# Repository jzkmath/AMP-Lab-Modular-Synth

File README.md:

# AMP Lab Modular Synth
This is a fully modular eurorack synthesizer project, where I design all the circuits myself, or do designs based off of existing modules.

All PCBs will be designed in KiCAD so that the entire project can be made open source and used by anyone interested. 

## Important Links:
[AMP Lab Project Page](https://sites.google.com/a/vt.edu/amp_lab/projects/modular-eurorack-synth)

[YuSynth](http://yusynth.net/Modular/modular.html) - Basis for some of the designs

[Moog Werkstatt](https://www.moogmusic.com/products/werkstatt-01) - Basis for some of the designs

## VCO

## VCF

## EG

## VCA

## MIDI Controller

## Power Supply

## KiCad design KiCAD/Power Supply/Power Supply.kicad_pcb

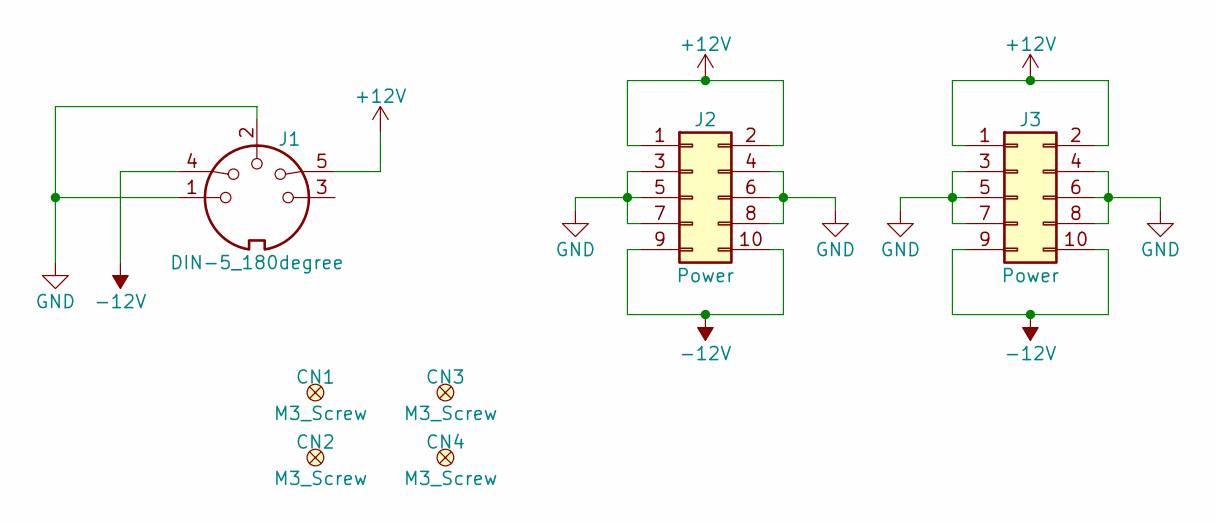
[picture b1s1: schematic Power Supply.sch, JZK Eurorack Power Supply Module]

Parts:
CN1, CN2, CN3, CN4: M3_Screw; M3_Screw_Hole; Digikey PN N/A
J1: DIN-5_180degree; PinHeader_1x05_P2.54mm_Vertical
J2, J3: Power; PinHeader_2x05_P2.54mm_Vertical_Zigzag

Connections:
+12V: J1.5, J2.1, J2.2, J3.1, J3.2
-12V: J1.4, J2.9, J2.10, J3.9, J3.10
GND: J1.1, J1.2, J2.3, J2.4, J2.5, J2.6, J2.7, J2.8, J3.3, J3.4, J3.5, J3.6, J3.7, J3.8

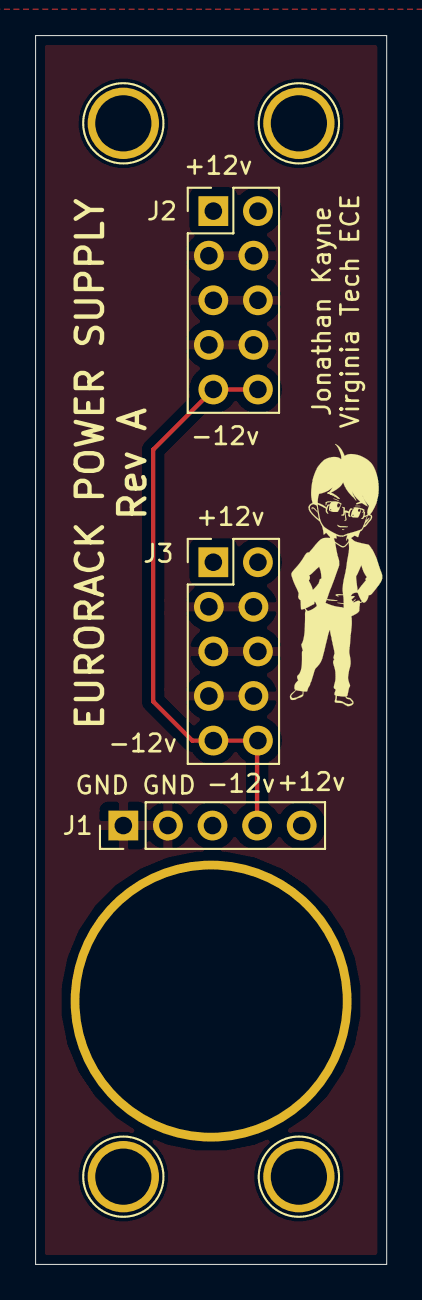
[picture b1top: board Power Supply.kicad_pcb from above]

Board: 2 copper layers, 20.0 x 70.0 mm, 7 parts (0 on the bottom side), 3 nets.

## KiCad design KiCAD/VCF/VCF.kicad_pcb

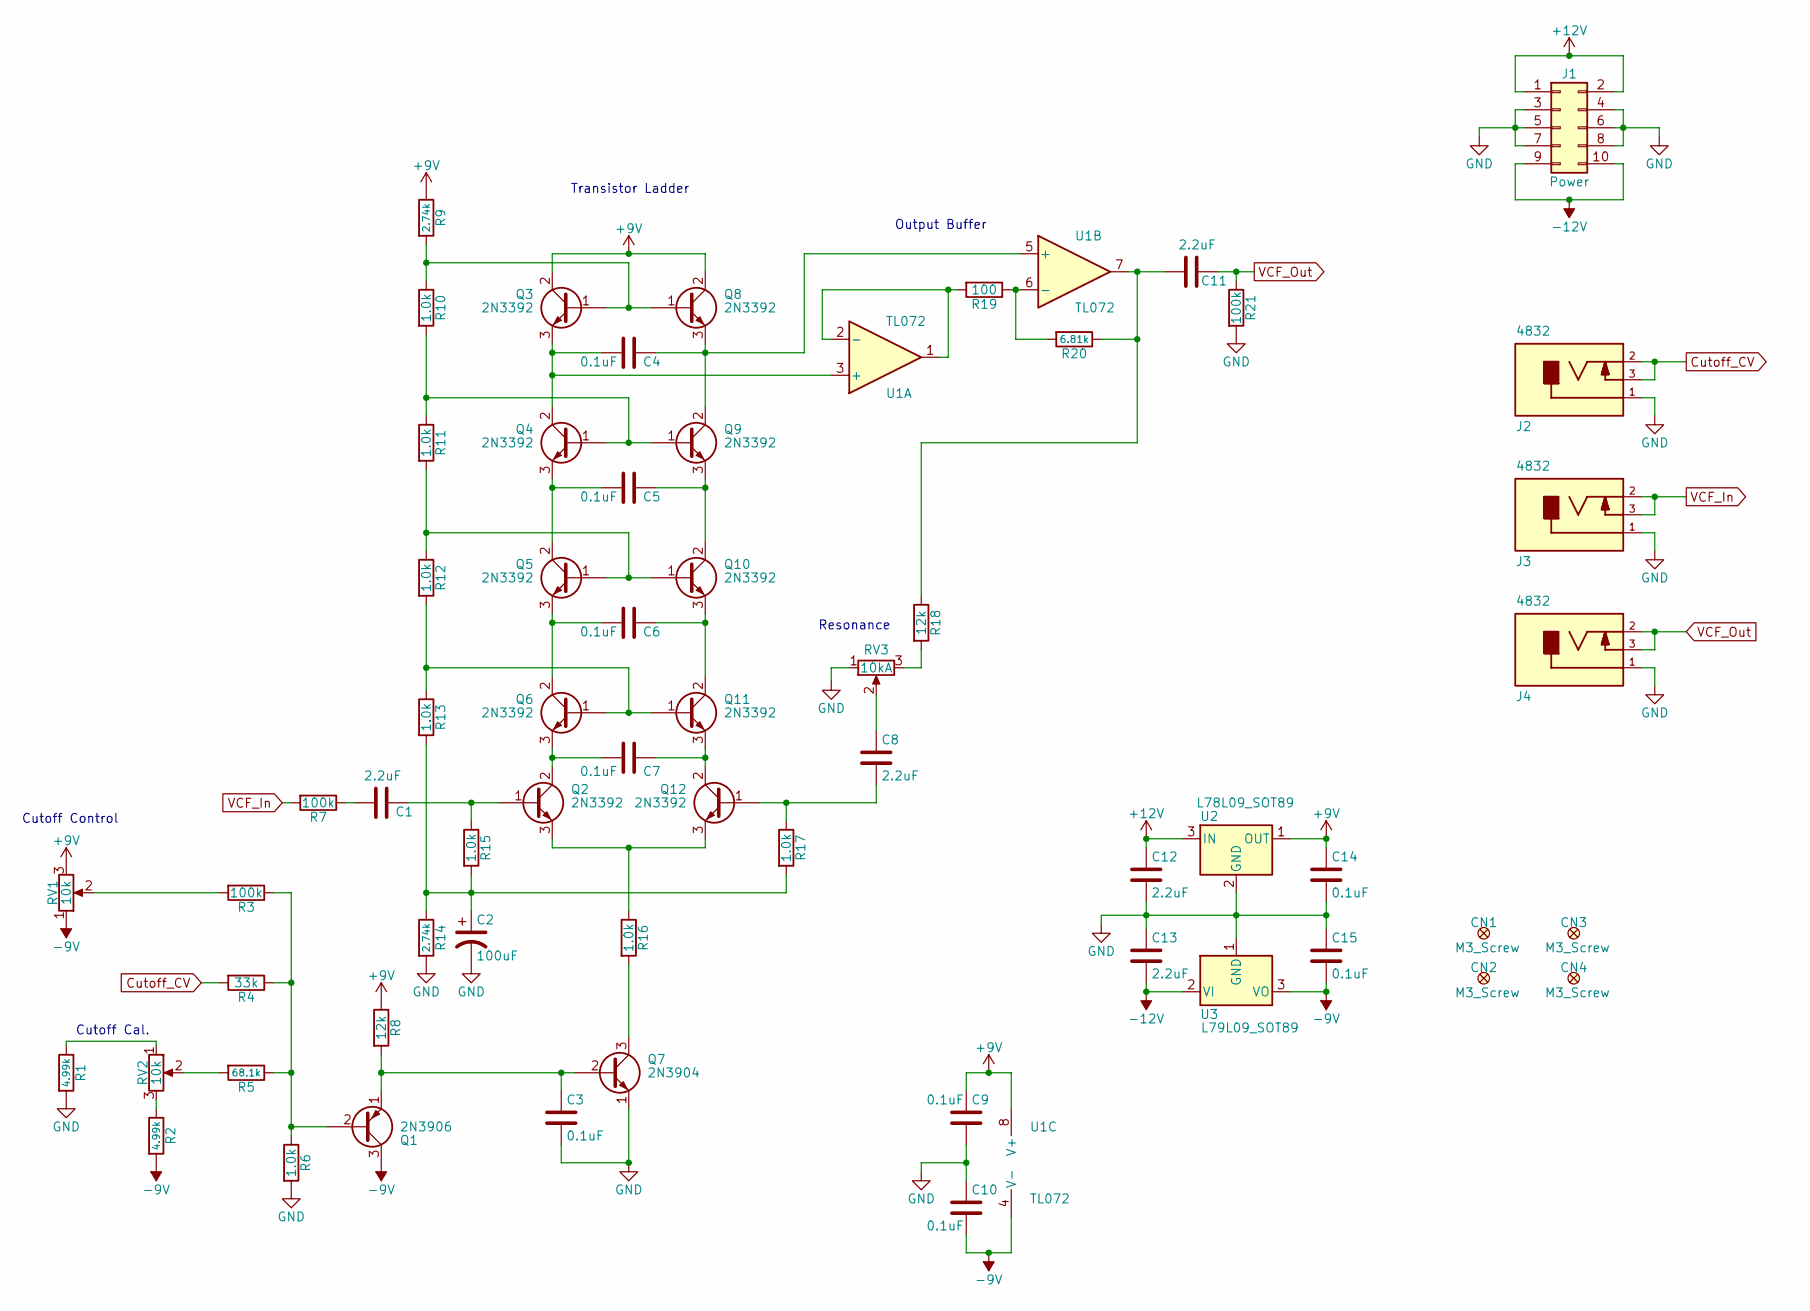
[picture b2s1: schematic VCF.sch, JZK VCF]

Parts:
C1, C8, C11, C12, C13: 2.2uF; C_1206; Digikey PN 1276-1072-1-ND
C2: 100uF; CP_Tantalum_7343; Digikey PN 399-9749-1-ND
C3, C4, C5, C6, C7, C9, C10, C14, C15: 0.1uF; C_1206; Digikey PN 720-1540-1-ND
CN1, CN2, CN3, CN4: M3_Screw; M3_Screw_Hole; Digikey Link N/A
J1: Power; PinHeader_2x05_P2.54mm_Vertical_Zigzag; Digikey PN 609-3243-ND
J2, J3, J4: 4832; Schurter_4832_Jack; Digikey PN 486-3418-ND
Q1: 2N3906; TO-92_HandSolder; Digikey PN 2N3906TARFSCT-ND
Q2, Q3, Q4, Q5, Q6, Q8, Q9, Q10, Q11, Q12: 2N3392; TO-92_HandSolder; Digikey PN 2N3392CS-ND
Q7: 2N3904; TO-92_HandSolder; Digikey PN 2N3904FS-ND
R1, R2: 4.99k; R_1206; Digikey PN RNCP1206FTD4K99CT-ND
R3, R7, R21: 100k; R_1206; Digikey PN A129834CT-ND
R4: 33k; R_1206; Digikey PN RMCF1206JT33K0CT-ND
R5: 68.1k; R_1206; Digikey PN RNCP1206FTD68K1CT-ND
R6, R10, R11, R12, R13, R15, R16, R17: 1.0k; R_1206; Digikey PN 311-1.0KERCT-ND
R8, R18: 12k; R_1206; Digikey PN A129823CT-ND
R9, R14: 2.74k; R_1206; Digikey PN 311-2.74KFRCT-ND
R19: 100; R_1206; Digikey PN RNCP1206FTD100RCT-ND
R20: 6.81k; R_1206; Digikey PN RNCP1206FTD6K81CT-ND
RV1: 10k; Potentiometer_Bourns_PTV09A-1_Single_Vertical; Digikey PN PTV09A-4020F-B103-ND
RV2: 10k; Potentiometer_Piher_PT-10-V10_Vertical; Digikey PN 1993-1104-ND
RV3: 10kA; Potentiometer_Bourns_PTV09A-1_Single_Vertical; Digikey PN PTV09A-4020F-A103-ND
U1: TL072; SOIC-8_3.9x4.9mm_P1.27mm; Digikey PN 296-1282-1-ND
U2: L78L09_SOT89; SOT-89-3; Digikey PN 497-1192-1-ND
U3: L79L09_SOT89; SOT-89-3; Digikey PN NJM79L09UA-TE1CT-ND

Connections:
+9V: C9.1, C14.1, Q3.2 (C), Q8.2 (C), R8.1, R9.1, RV1.3, U1.8 (V+), U2.1 (OUT)
+12V: C12.1, J1.1, J1.2, U2.3 (IN)
-9V: C10.2, C15.2, Q1.3 (C), R2.2, RV1.1, U1.4 (V-), U3.3 (VO)
-12V: C13.2, J1.9, J1.10, U3.2 (VI)
Cutoff_CV: J2.2, J2.3, R4.2
GND: C2.2, C3.2, C9.2, C10.1, C12.2, C13.1, C14.2, C15.1, J1.3, J1.4, J1.5, J1.6, J1.7, J1.8, J2.1, J3.1, J4.1, Q7.1 (E), R1.2, R6.2, R14.2, R21.2, RV3.1, U2.2 (GND), U3.1 (GND)
unnamed: C1.1, Q2.1 (B), R15.1
unnamed: C1.2, R7.1
unnamed: C2.1, R13.2, R14.1, R15.2, R17.2
unnamed: C3.1, Q1.1 (E), Q7.2 (B), R8.2
unnamed: C4.1, Q8.3 (E), Q9.2 (C), U1.5 (+)
unnamed: C4.2, Q3.3 (E), Q4.2 (C), U1.3 (+)
unnamed: C5.1, Q9.3 (E), Q10.2 (C)
unnamed: C5.2, Q4.3 (E), Q5.2 (C)
unnamed: C6.1, Q10.3 (E), Q11.2 (C)
unnamed: C6.2, Q5.3 (E), Q6.2 (C)
unnamed: C7.1, Q11.3 (E), Q12.2 (C)
unnamed: C7.2, Q2.2 (C), Q6.3 (E)
unnamed: C8.1, RV3.2
unnamed: C8.2, Q12.1 (B), R17.1
unnamed: C11.2, R18.1, R20.1, U1.7
unnamed: Q1.2 (B), R3.1, R4.1, R5.1, R6.1
unnamed: Q3.1 (B), Q8.1 (B), R9.2, R10.1
unnamed: Q4.1 (B), Q9.1 (B), R10.2, R11.1
unnamed: Q7.3 (C), R16.2
unnamed: Q5.1 (B), Q10.1 (B), R11.2, R12.1
unnamed: Q6.1 (B), Q11.1 (B), R12.2, R13.1
unnamed: Q2.3 (E), Q12.3 (E), R16.1
unnamed: R1.1, RV2.1
unnamed: R2.1, RV2.3
unnamed: R3.2, RV1.2
unnamed: R5.2, RV2.2
unnamed: R18.2, RV3.3
unnamed: R19.1, R20.2, U1.6 (-)
unnamed: R19.2, U1.1, U1.2 (-)
VCF_In: J3.2, J3.3, R7.2
VCF_Out: C11.1, J4.2, J4.3, R21.1

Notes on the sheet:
Cutoff Control
Cutoff Cal.
Transistor Ladder
Output Buffer
Resonance

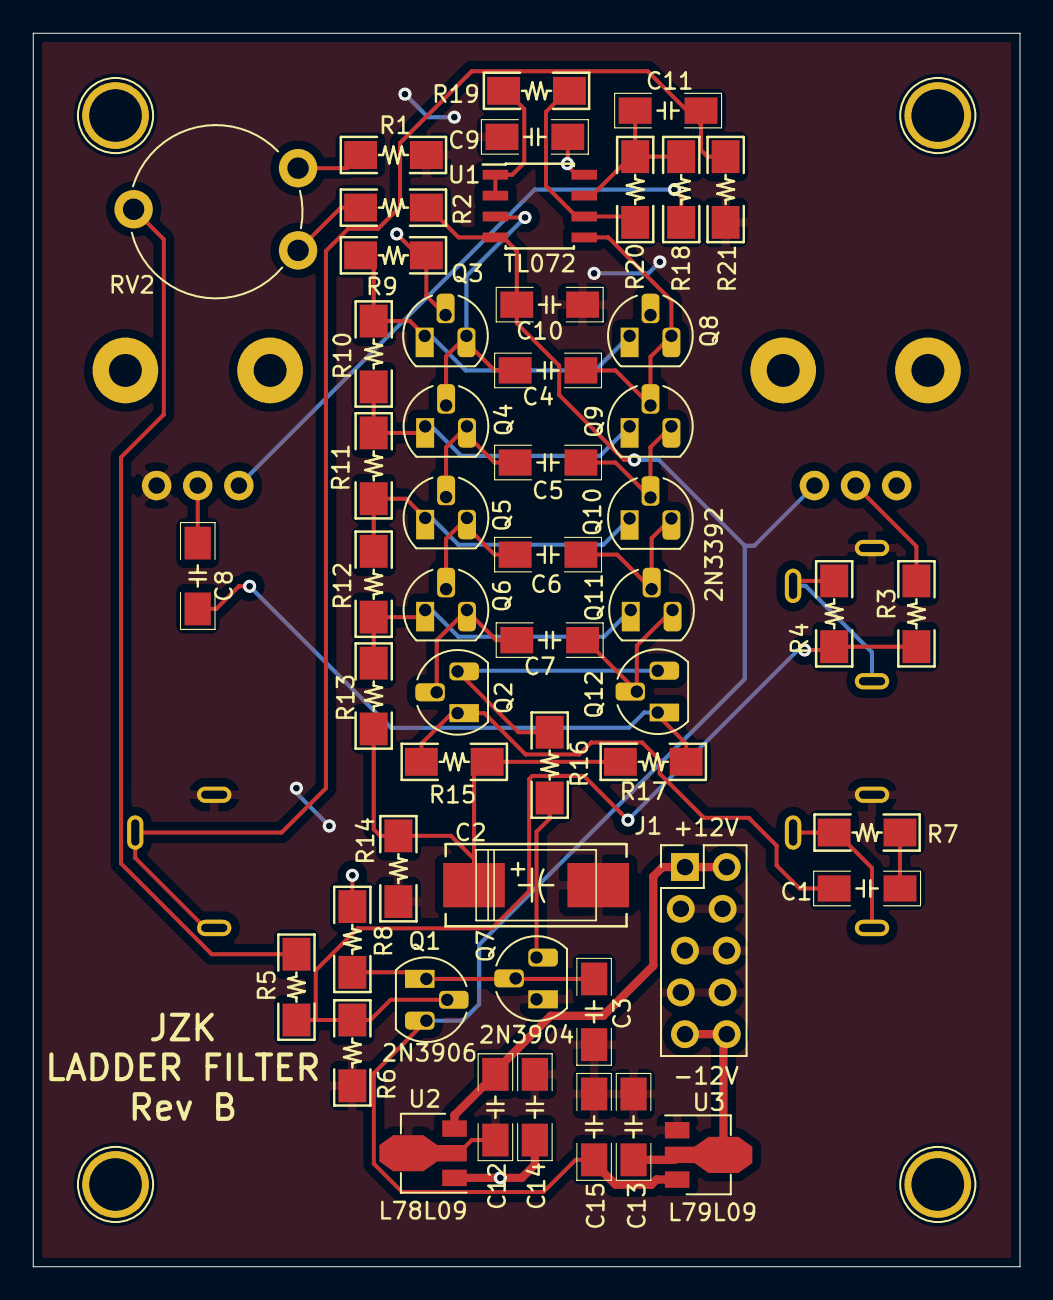
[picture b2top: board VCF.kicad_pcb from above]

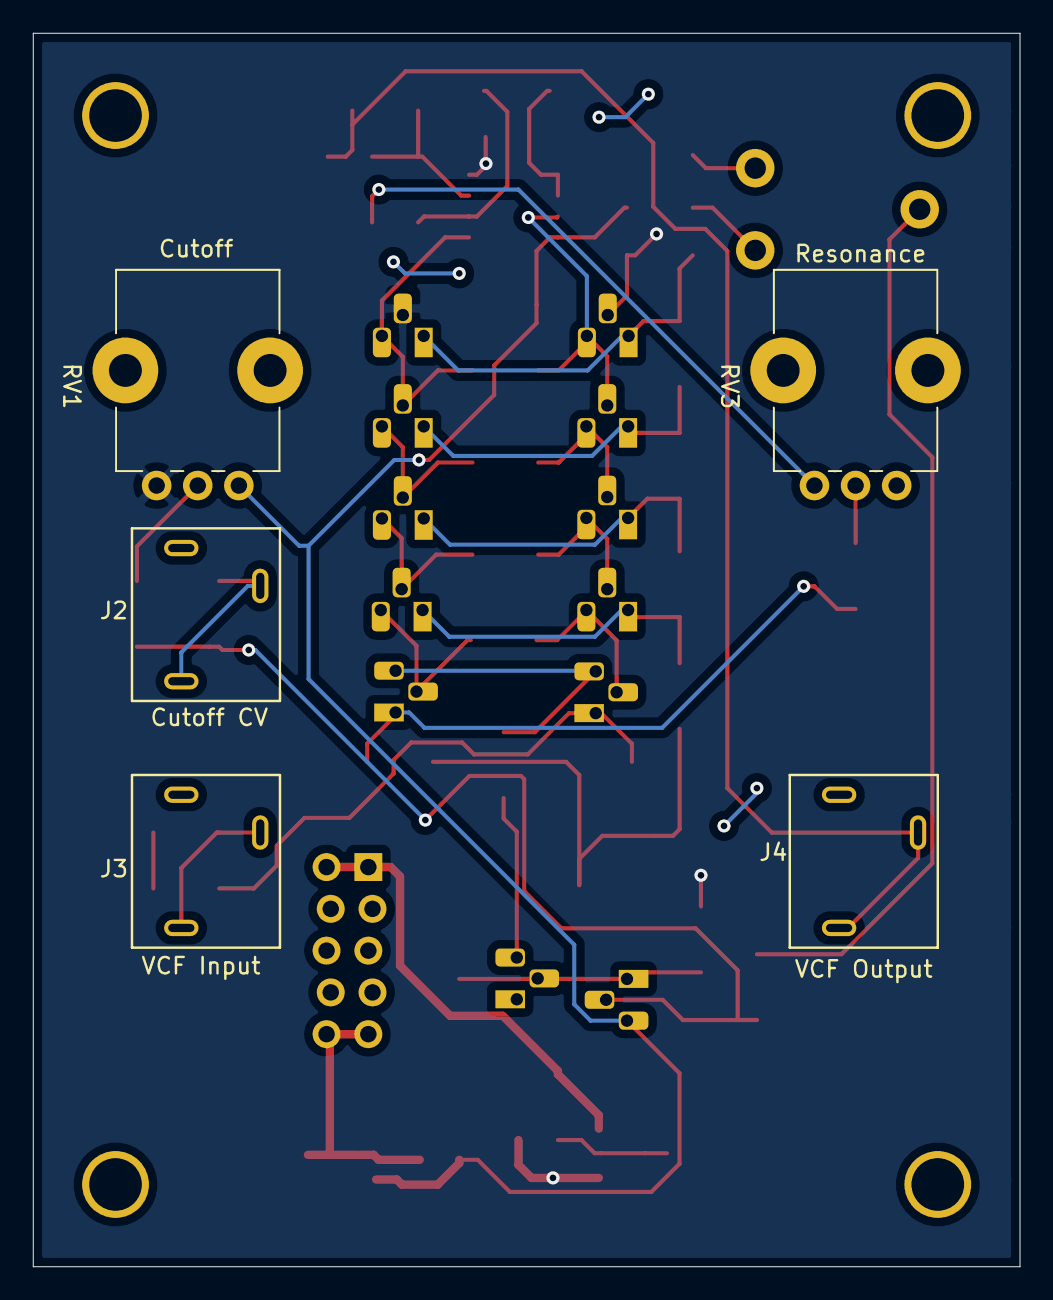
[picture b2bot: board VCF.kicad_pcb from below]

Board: 2 copper layers, 60.0 x 75.0 mm, 62 parts (5 on the bottom side), 37 nets.

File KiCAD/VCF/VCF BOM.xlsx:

Item | Qty | Reference(s) | Value | Footprint | Cost ea | Total Cost | Digikey PN | Link | Total: | 22.346000000000011
1 | 5 | C1, C8, C11-C13 | 2.2uF | SMD 1206 | 0.22 | 1.1000000000000001 | 1276-1072-1-ND | https://www.digikey.com/short/pzvv0r
2 | 1 | C2 | 100uF | SMD 7343 | 2.71 | 2.71 | 399-9749-1-ND | https://www.digikey.com/short/pzvvbz
3 | 9 | C3-C7, C9, C10, C14, C15 | 0.1uF | SMD 1206 | 8.7999999999999995E-2 | 0.79199999999999993 | 1276-1017-1-ND | https://www.digikey.com/short/pzb5jq
4 | 1 | J1 | Power | 2x5 Header | 0.28000000000000003 | 0.28000000000000003 | 609-3243-ND | https://www.digikey.com/short/pzbbv4
5 | 3 | J2-J4 | MJ-3502 | HP Jack | 1.5 | 4.5 | 486-3418-ND | https://www.digikey.com/short/pzbbdf
6 | 1 | Q1 | 2N3906 | TO-92 | 0.24 | 0.24 | 2N3906TARFSCT-ND | https://www.digikey.com/short/pzvv5n
7 | 10 | Q2-Q6, Q8-Q12 | 2N3392 | TO-92 | 0.66800000000000004 | 6.6800000000000006 | 2N3392CS-ND | https://www.digikey.com/short/pzvv5p
8 | 1 | Q7 | 2N3904 | TO-92 | 0.21 | 0.21 | 2N3904FS-ND | https://www.digikey.com/short/pzvv5m
9 | 2 | R1, R2 | 4.99k | SMD 1206 | 0.1 | 0.2 | RNCP1206FTD4K99CT-ND | https://www.digikey.com/short/pzvvn3
10 | 3 | R3, R7, R21 | 100k | SMD 1206 | 7.0000000000000007E-2 | 0.21000000000000002 | A129834CT-ND | https://www.digikey.com/short/pzb5r0
11 | 1 | R4 | 33k | SMD 1206 | 0.1 | 0.1 | RMCF1206JT33K0CT-ND | https://www.digikey.com/short/pzbr3z
12 | 1 | R5 | 68.1k | SMD 1206 | 0.1 | 0.1 | RNCP1206FTD68K1CT-ND | https://www.digikey.com/short/pzvvnh
13 | 8 | R6, R10-R13, R15-R17 | 1.0k | SMD 1206 | 9.2999999999999999E-2 | 0.74399999999999999 | RNCP1206FTD1K00CT-ND | https://www.digikey.com/short/pzvvnv
14 | 2 | R8, R18 | 12k | SMD 1206 | 0.1 | 0.2 | A129823CT-ND | https://www.digikey.com/short/pzvvdq
15 | 2 | R9, R14 | 2.74k | SMD 1206 | 0.1 | 0.2 | 311-2.74KFRCT-ND | https://www.digikey.com/short/pzvvd5
16 | 1 | R19 | 100 ohm | SMD 1206 | 0.1 | 0.1 | RNCP1206FTD100RCT-ND | https://www.digikey.com/short/pzvvdd
17 | 1 | R20 | 6.81k | SMD 1206 | 0.1 | 0.1 | RNCP1206FTD6K81CT-ND | https://www.digikey.com/short/pzvv07
18 | 2 | RV1, RV3 | 25k | THT Pot | 0.79 | 1.58 | 987-1726-ND | https://www.digikey.com/short/pzb2f3
19 | 1 | RV2 | 10k | Trimpot | 0.46 | 0.46 | 1993-1104-ND | https://www.digikey.com/short/pzzwhq
20 | 1 | U1 | TL072 | SOIC8 | 0.62 | 0.62 | 296-1282-1-ND | https://www.digikey.com/short/pzvvrz
21 | 1 | U2 | L78L09 | SOT-89 | 0.42 | 0.42 | 497-1192-1-ND | https://www.digikey.com/short/pz1hnp
22 | 1 | U3 | L79L09 | SOT-89 | 0.8 | 0.8 | NJM79L09UA-TE1CT-ND | https://www.digikey.com/short/pz1hn5
 |  |  |  |  |  | 0
 |  |  |  |  |  | 0

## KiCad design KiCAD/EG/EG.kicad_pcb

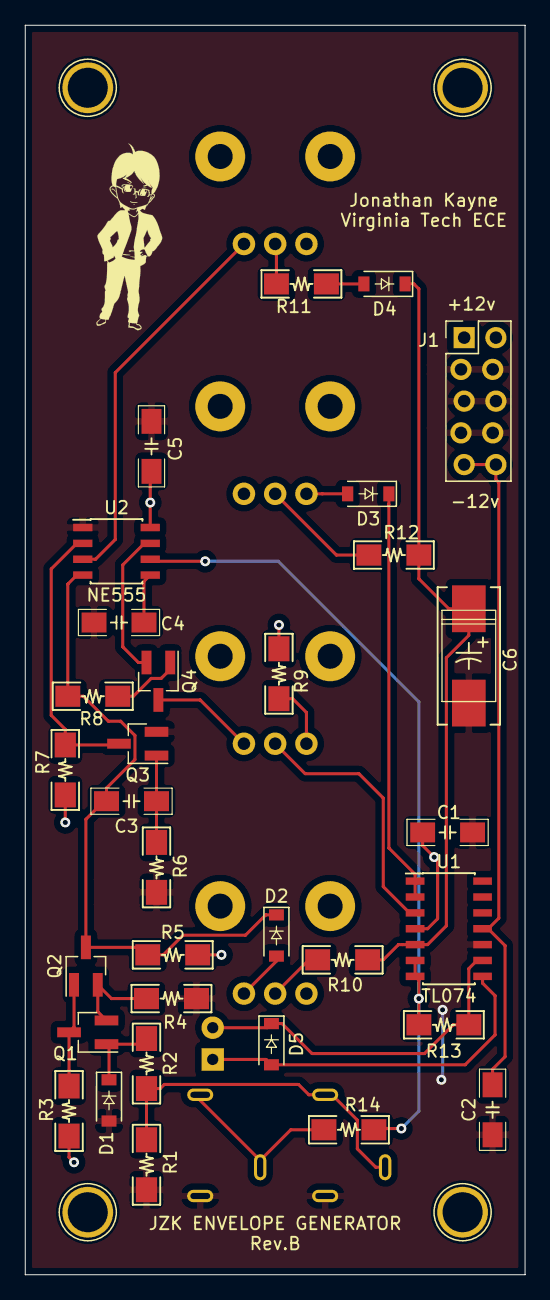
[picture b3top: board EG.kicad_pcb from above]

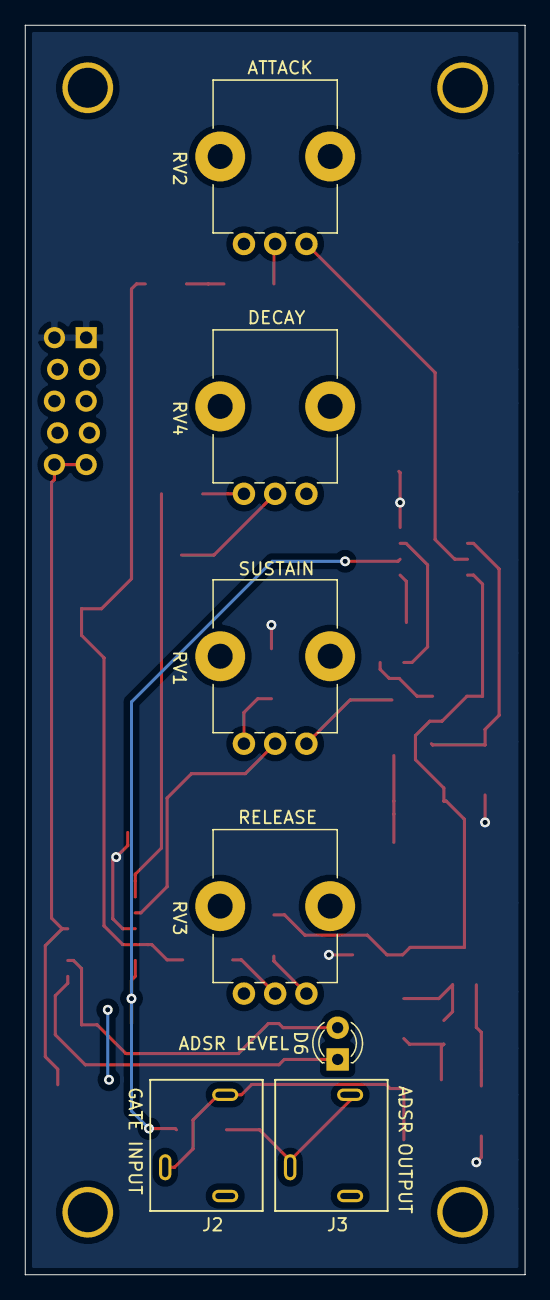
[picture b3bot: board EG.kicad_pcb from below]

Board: 2 copper layers, 40.0 x 100.0 mm, 43 parts (7 on the bottom side), 29 nets.

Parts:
C1, C2, C5: 0.1uF; C_1206
C3, C4: 10nF; C_1206
C6: 10uF; CP_Tantalum_7343
CN1, CN2, CN3, CN4: M3_Screw; M3_Screw_Hole
D1, D2, D3, D4, D5: 1N4148W; D_SOD-123
D6: LED; LED_D3.0mm_Clear
J1: Power; PinHeader_2x05_P2.54mm_Vertical_Zigzag
J2, J3: 4832; Schurter_4832_Jack
Q1, Q2, Q3: BC847; SOT-23_Handsoldering
Q4: 2N7002; SOT-23_Handsoldering
R1: 1.2M; R_1206
R2, R8: 1M; R_1206
R3, R5, R6, R7: 22k; R_1206
R4: 10; R_1206
R9: 4.7k; R_1206
R10, R11, R12: 100; R_1206
R13, R14: 1k; R_1206
RV1: 25k; Potentiometer_Bourns_PTV09A-1_Single_Vertical
RV2, RV3, RV4: 1M Log; Potentiometer_Bourns_PTV09A-1_Single_Vertical
U1: TL074; SOIC-14_3.9x8.7mm_P1.27mm
U2: NE555; SOIC-8_3.9x4.9mm_P1.27mm

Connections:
+12V: C1.1, C5.2, J1.1, J1.2, R3.1, R5.1, R7.1, R9.1, U1.4, U2.8
-12V: C2.2, J1.9, J1.10, U1.11
/Attack: R11.2, RV2.2
/Decay: R12.1, RV4.2
/Release: R10.2, RV3.2
/Sustain: RV1.2, U1.3
ADSR_Out: J3.2, J3.3, R14.1
EG_Out: R13.2, R14.2, U1.6, U1.7, U2.6
GND: C1.2, C2.1, C4.2, C5.1, C6.2, D1.2, J1.3, J1.4, J1.5, J1.6, J1.7, J1.8, J2.1, J3.1, Q3.2, R1.2, R4.2, R6.2, U1.10, U2.1
Gate_In: J2.2, J2.3, R1.1, R2.2
unnamed: C3.1, Q3.1, R6.1
unnamed: C3.2, D2.1, Q2.3, R5.2, R8.2, U2.4
unnamed: C4.1, U2.5
unnamed: C6.1, D4.1, R10.1, R12.2, U1.5
unnamed: D1.1, Q1.1, R2.1
unnamed: D2.2, RV3.1
unnamed: D3.1, U1.1, U1.2
unnamed: D3.2, RV4.3
unnamed: D4.2, R11.1
unnamed: D5.1, D6.2, R13.1, U1.9
unnamed: D5.2, D6.1, U1.8
unnamed: Q1.2, Q2.2, R4.1
unnamed: Q1.3, Q2.1, R3.2
unnamed: Q3.3, R7.2, U2.2
unnamed: Q4.1, R8.1
unnamed: Q4.2, U2.7
unnamed: Q4.3, RV1.1
unnamed: R9.2, RV1.3
unnamed: RV2.1, U2.3

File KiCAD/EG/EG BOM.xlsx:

Item | Qty | Reference(s) | Value | Footprint | Cost ea | Total Cost | Digikey | Link | Final Cost: | 12.316999999999998
1 | 3 | C1, C2, C5 | 0.1uF | SMD 1206 | 8.7999999999999995E-2 | 0.26400000000000001 | 1276-1017-1-ND | https://www.digikey.com/short/pzb5jq |  |  |  | p
2 | 2 | C3, C4 | 10nF | SMD 1206 | 0.27 | 0.54 | 311-1174-1-ND | https://www.digikey.com/short/p47c0p |  |  |  | p
3 | 1 | C6 | 10uF | SMD 7343 | 0.73 | 0.73 | 718-1046-1-ND | https://www.digikey.com/short/p47cw2 |  |  |  | p
4 | 5 | D1-D5 | 1N4148W | SOD-123 | 0.125 | 0.625 | 1N4148WTPMSCT-ND | https://www.digikey.com/short/pzz2zr |  |  |  | p
5 | 1 | D6 | LED | LED | 0 | 0 | Already Have
6 | 1 | J1 | Power | 2x5 Header | 0.28000000000000003 | 0.28000000000000003 | 609-3243-ND | https://www.digikey.com/short/pzbbv4 |  |  |  | p
7 | 2 | J2, J3 | MJ-3502 | HP Jack | 1.5 | 3 | 486-3418-ND | https://www.digikey.com/short/pzbbdf |  |  |  | p
8 | 3 | Q1, Q2, Q3 | BC847 | SOT-23 | 0.129 | 0.38700000000000001 | BC847CLT1GOSCT-ND | https://www.digikey.com/short/p47c90 |  |  |  | p
9 | 1 | Q4 | 2N7002 | SOT-23 | 0.39 | 0.39 | 2N7002NCT-ND | https://www.digikey.com/short/p47cfq |  |  |  | p
10 | 1 | R1 | 1.2M | SMD 1206 | 0.1 | 0.1 | 311-1.20MFRCT-ND | https://www.digikey.com/short/p477qb |  |  |  | p
11 | 2 | R2, R8 | 1M | SMD 1206 | 0.1 | 0.2 | RMCF1206JT1M00CT-ND | https://www.digikey.com/short/pzbrq5 |  |  |  | p
12 | 4 | R3, R5-R7 | 22k | SMD 1206 | 0.27800000000000002 | 1.1120000000000001 | A130554CT-ND | https://www.digikey.com/short/p477jj |  |  |  | p
13 | 1 | R4 | 10 ohm | SMD 1206 | 0.17 | 0.17 | P10ALCT-ND | https://www.digikey.com/short/pzbrph |  |  |  | p
14 | 1 | R9 | 4.7k | SMD 1206 | 0.1 | 0.1 | A130181CT-ND | https://www.digikey.com/short/pzbrh2 |  |  |  | p
15 | 3 | R10-R12 | 100 ohm | SMD 1206 | 0.1 | 0.30000000000000004 | RNCP1206FTD100RCT-ND | https://www.digikey.com/short/pzvvdd |  |  |  | p
16 | 2 | R13, R14 | 1k | SMD 1206 | 0.1 | 0.2 | 311-1.0KERCT-ND | https://www.digikey.com/short/pzbr9h |  |  |  | p
17 | 1 | RV1 | 25k | Pot | 0.79 | 0.79 | 987-1726-ND | https://www.digikey.com/short/pzb2f3 |  |  |  | p
18 | 3 | RV2-RV4 | 1M Log | Pot | 0.71299999999999997 | 2.1389999999999998 | 987-1719-ND | https://www.digikey.com/short/p477bw |  |  |  | p
19 | 1 | U1 | TL074 | SOIC-14 | 0.51 | 0.51 | 296-1283-1-ND | https://www.digikey.com/short/pzz2fn |  |  |  | p
20 | 1 | U2 | NE555 | SOIC-8 | 0.48 | 0.48 | 296-6501-1-ND | https://www.digikey.com/short/p47c41 |  |  |  | p
 |  |  |  |  |  | 0
 |  |  |  |  |  | 0
 |  |  |  |  |  | 0
 |  |  |  |  |  | 0

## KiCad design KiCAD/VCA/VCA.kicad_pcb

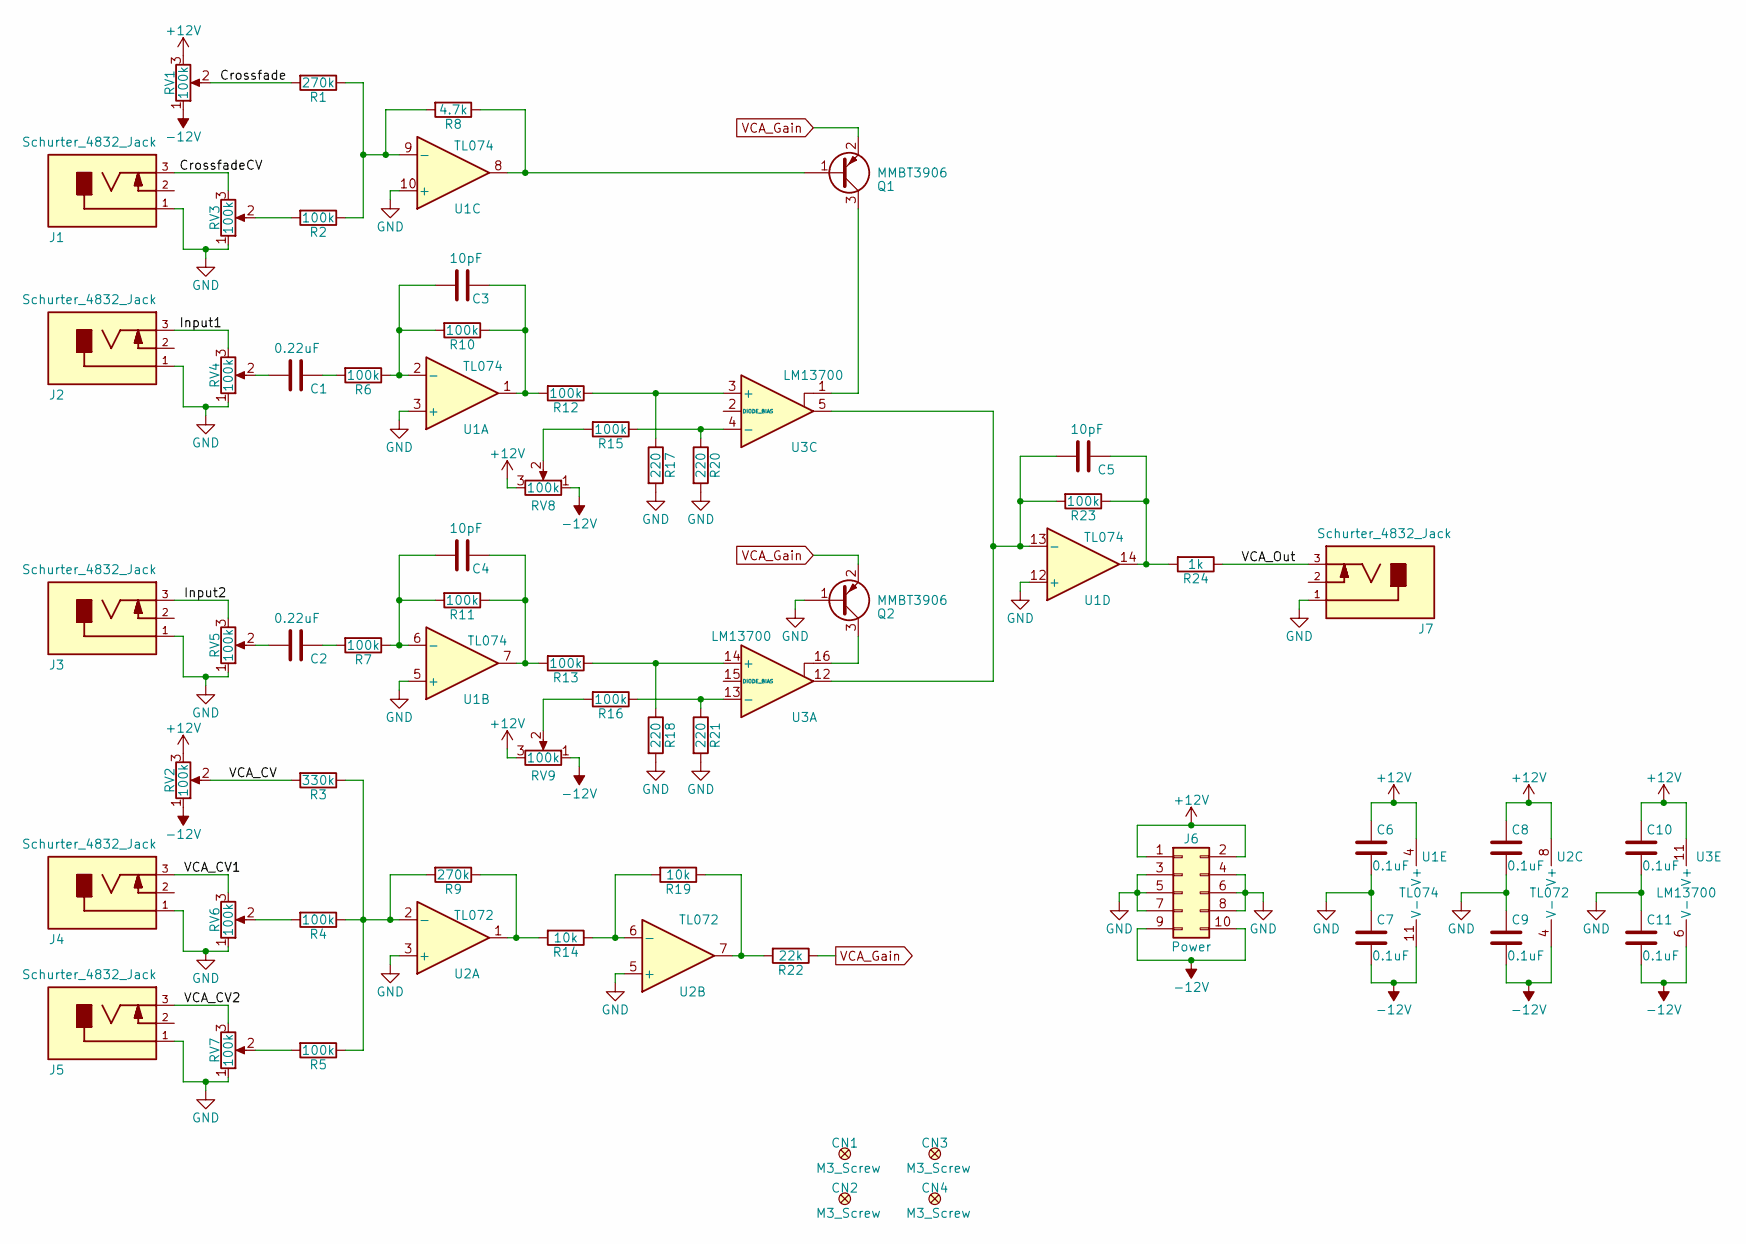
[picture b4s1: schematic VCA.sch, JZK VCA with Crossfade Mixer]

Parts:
C1, C2: 0.22uF; C_1206; Digikey PN 445-2283-1-ND
C3, C4, C5: 10pF; C_1206; Digikey PN 311-1150-1-ND
C6, C7, C8, C9, C10, C11: 0.1uF; C_1206; Digikey PN 720-1540-1-ND
CN1, CN2, CN3, CN4: M3_Screw; M3_Screw_Hole; Digikey Link N/A
J1, J2, J3, J4, J5, J7: Schurter_4832_Jack; Digikey PN 486-3418-ND
J6: Power; PinHeader_2x05_P2.54mm_Vertical_Zigzag; Digikey PN 609-3243-ND
Q1, Q2: MMBT3906; SOT-23_Handsoldering; Digikey PN MMBT3906LT1GOSCT-ND
R1, R9: 270k; R_1206; Digikey PN A129839CT-ND
R2, R4, R5, R6, R7, R10, R11, R12, R13, R15, R16, R23: 100k; R_1206; Digikey PN A129834CT-ND
R3: 330k; R_1206; Digikey PN P330KBCCT-ND
R8: 4.7k; R_1206; Digikey PN A130181CT-ND
R14, R19: 10k; R_1206; Digikey PN RMCF1206JT10K0CT-ND
R17, R18, R20, R21: 220; R_1206; Digikey PN 311-220FRCT-ND
R22: 22k; R_1206; Digikey PN A130554CT-ND
R24: 1k; R_1206; Digikey PN 311-1.0KERCT-ND
RV1, RV2, RV3, RV4, RV5, RV6, RV7: 100k; Potentiometer_Bourns_PTV09A-1_Single_Vertical; Digikey PN PTV09A-4020F-B104-ND
RV8, RV9: 100k; Trimpot_Bourns_3306F; Digikey PN 3306F-104-ND
U1: TL074; SOIC-14_3.9x8.7mm_P1.27mm; Digikey PN 296-1283-1-ND
U2: TL072; SOIC-8_3.9x4.9mm_P1.27mm; Digikey PN 296-1282-1-ND
U3: LM13700; SOIC-16_3.9x9.9mm_P1.27mm; Digikey PN LM13700MX/NOPBCT-ND

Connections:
+12V: C6.1, C8.1, C10.1, J6.1, J6.2, RV1.3, RV2.3, RV8.3, RV9.3, U1.4 (V+), U2.8 (V+), U3.11 (V+)
-12V: C7.2, C9.2, C11.2, J6.9, J6.10, RV1.1, RV2.1, RV8.1, RV9.1, U1.11 (V-), U2.4 (V-), U3.6 (V-)
/Crossfade: R1.2, RV1.2
/CrossfadeCV: J1.3, RV3.3
/Input1: J2.3, RV4.3
/Input2: J3.3, RV5.3
/VCA_CV: R3.2, RV2.2
/VCA_CV1: J4.3, RV6.3
/VCA_CV2: J5.3, RV7.3
/VCA_Out: J7.3, R24.1
GND: C6.2, C7.1, C8.2, C9.1, C10.2, C11.1, J1.1, J2.1, J3.1, J4.1, J5.1, J6.3, J6.4, J6.5, J6.6, J6.7, J6.8, J7.1, Q2.1 (B), R17.2, R18.2, R20.2, R21.2, RV3.1, RV4.1, RV5.1, RV6.1, RV7.1, U1.3 (+), U1.5 (+), U1.10 (+), U1.12 (+), U2.3 (+), U2.5 (+)
unnamed: C1.1, R6.2
unnamed: C1.2, RV4.2
unnamed: C2.1, R7.2
unnamed: C2.2, RV5.2
unnamed: C3.1, R10.1, R12.2, U1.1
unnamed: C3.2, R6.1, R10.2, U1.2 (-)
unnamed: C4.1, R11.1, R13.2, U1.7
unnamed: C4.2, R7.1, R11.2, U1.6 (-)
unnamed: C5.1, R23.1, R24.2, U1.14
unnamed: C5.2, R23.2, U1.13 (-), U3.5, U3.12
unnamed: Q1.1 (B), R8.1, U1.8
unnamed: Q1.3 (C), U3.1
unnamed: Q2.3 (C), U3.16
unnamed: R1.1, R2.1, R8.2, U1.9 (-)
unnamed: R2.2, RV3.2
unnamed: R3.1, R4.1, R5.1, R9.2, U2.2 (-)
unnamed: R4.2, RV6.2
unnamed: R5.2, RV7.2
unnamed: R12.1, R17.1, U3.3 (+)
unnamed: R13.1, R18.1, U3.14 (+)
unnamed: R14.1, R19.2, U2.6 (-)
unnamed: R9.1, R14.2, U2.1
unnamed: R15.1, R20.1, U3.4 (-)
unnamed: R15.2, RV8.2
unnamed: R16.1, R21.1, U3.13 (-)
unnamed: R16.2, RV9.2
unnamed: R19.1, R22.2, U2.7
VCA_Gain: Q1.2 (E), Q2.2 (E), R22.1

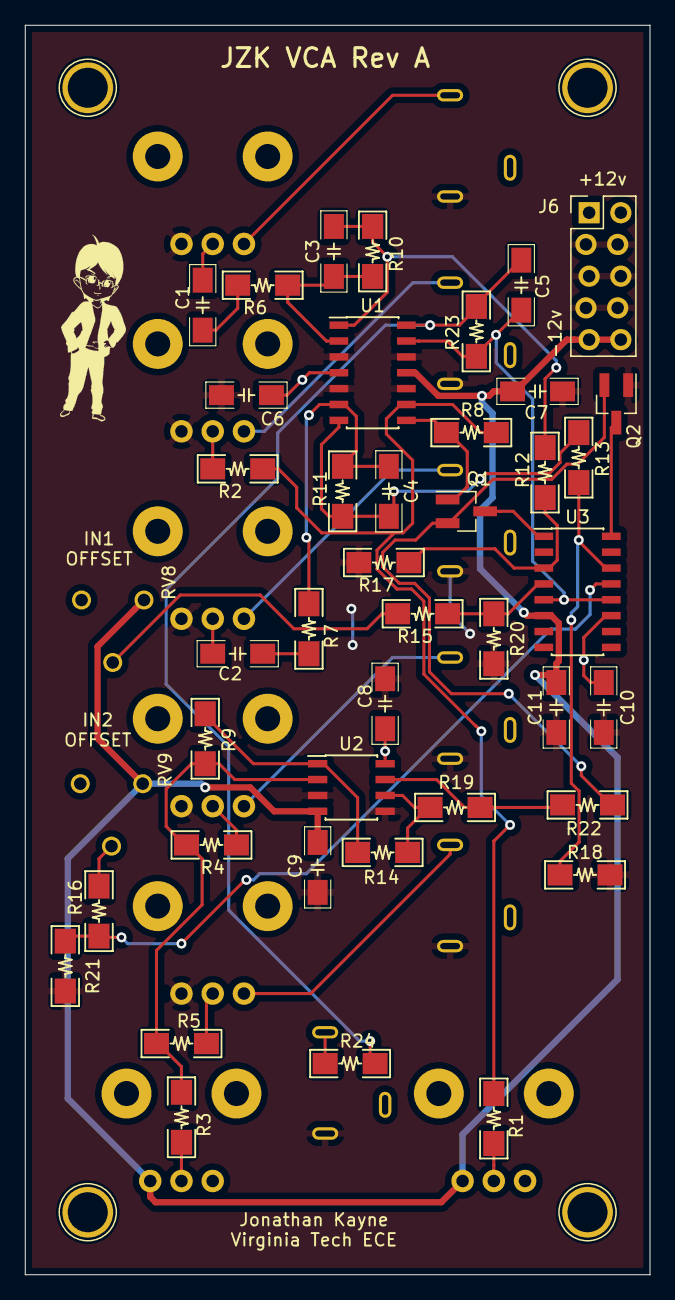
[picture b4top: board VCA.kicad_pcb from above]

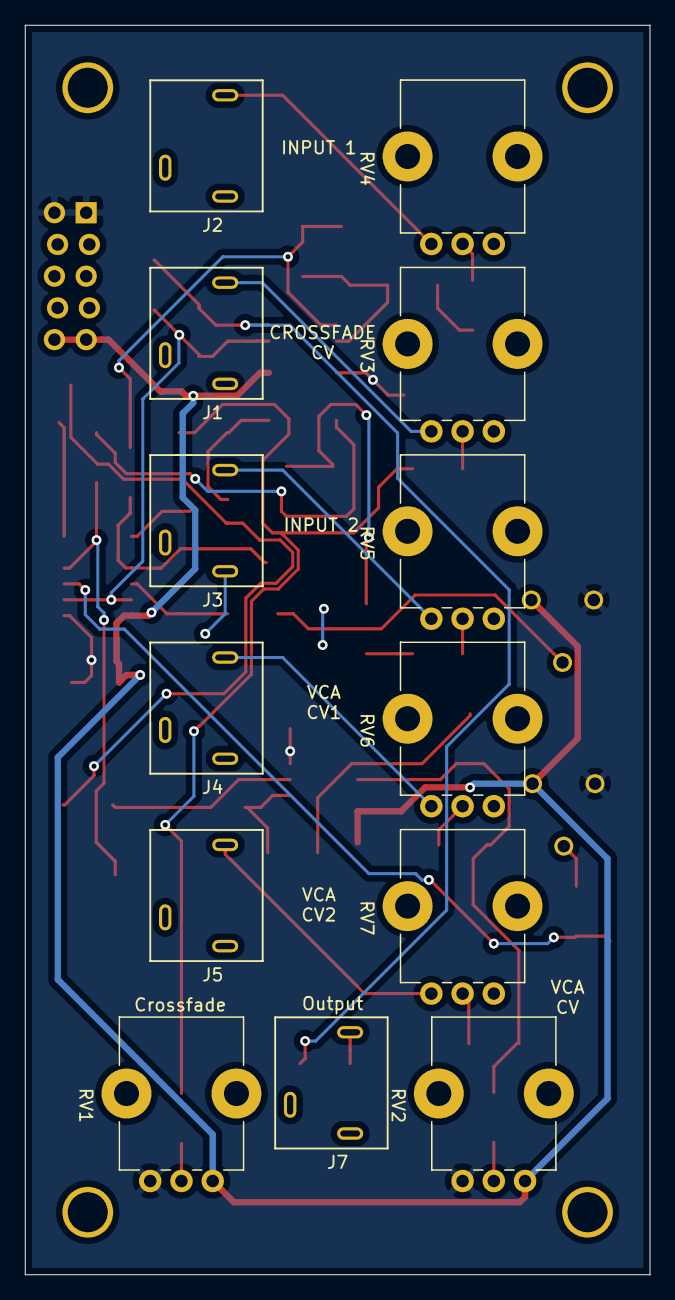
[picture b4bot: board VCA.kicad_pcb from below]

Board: 2 copper layers, 50.0 x 100.0 mm, 60 parts (13 on the bottom side), 39 nets.
